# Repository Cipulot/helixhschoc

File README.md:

# Helix HS Choc

Hotswap Choc version of the Helix, a compact split ortholinear keyboard.

Original Helix keyboard was designed by [Makoto Kurauchi](https://github.com/MakotoKurauchi).

## Documents

* Build Guide - [JP](/Doc/buildguide_jp.md), [EN](/Doc/buildguide_en.md)
* Firmware - [JP](/Doc/firmware_jp.md), [EN](/Doc/firmware_en.md)
* Usage - [JP](/Doc/usage_jp.md), [EN](/Doc/usage_en.md)

## Tool & Data

* [PCB Data](/PCB)
* [Case Data](/Case)
* [Font Converter](/FontConverter)

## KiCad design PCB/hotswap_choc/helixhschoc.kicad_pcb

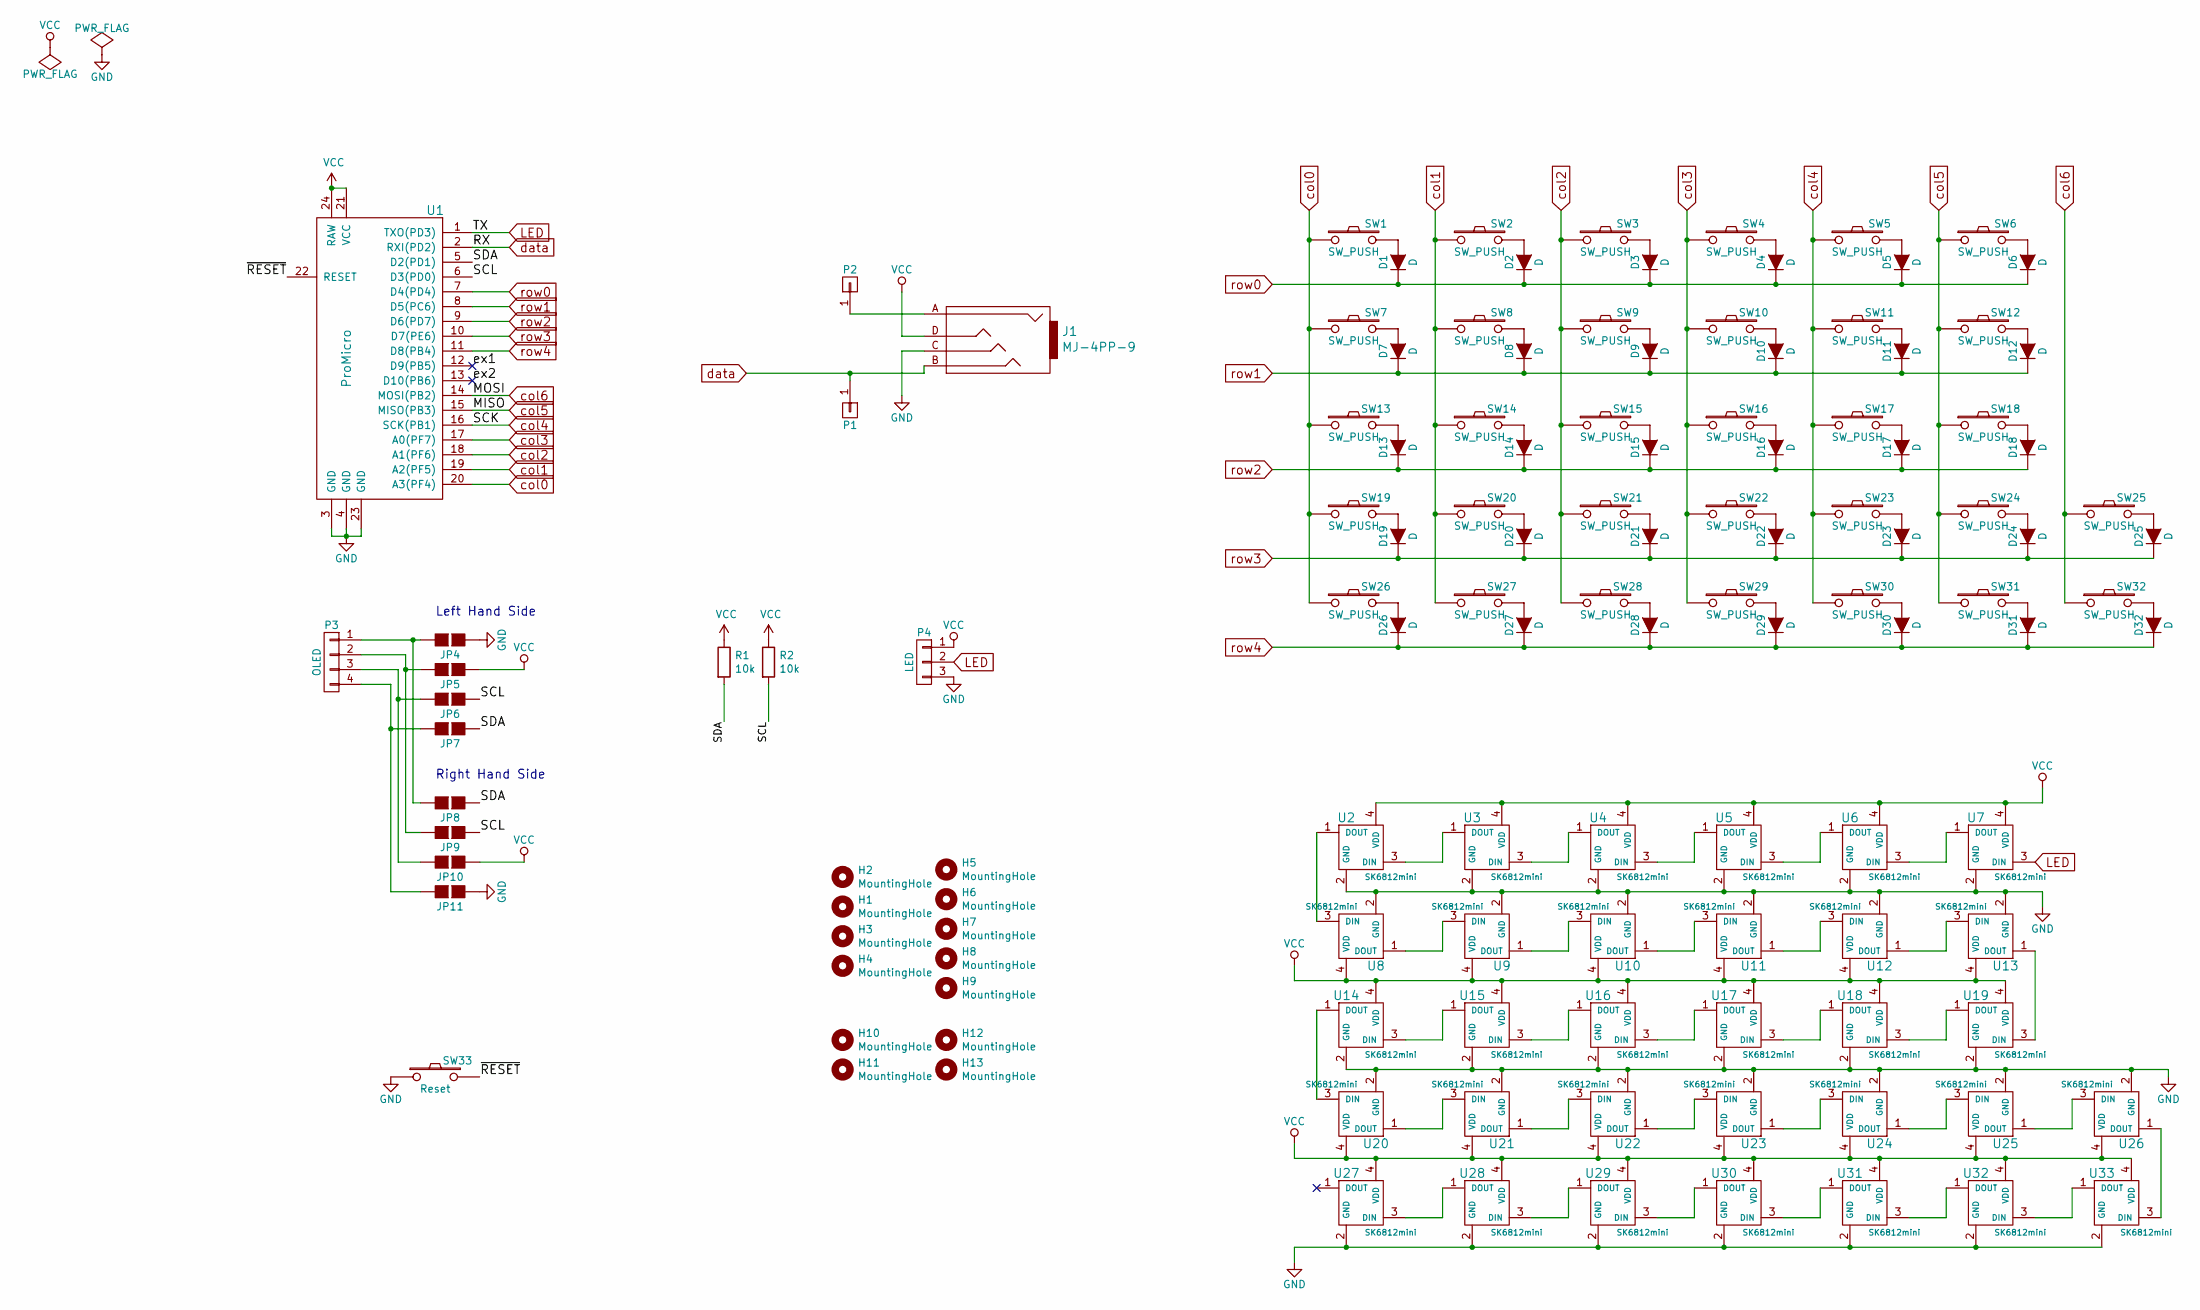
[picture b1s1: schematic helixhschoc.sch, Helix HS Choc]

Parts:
D1, D2, D3, D4, D5, D6, D7, D8, D9, D10, D11, D12, D13, D14, D15, D16, D17, D18, D19, D20, D21, D22, D23, D24, D25, D26, D27, D28, D29, D30, D31, D32: D; D_SOD-123_dual_reversed
H1, H2, H3, H4, H5, H6, H7, H8, H9: MountingHole; HOLE_M2_TH
H10, H11, H12, H13: MountingHole; HOLE_M2
J1: MJ-4PP-9
JP4, JP11: GND; Jumper_Small
JP5, JP10: VCC; Jumper_Small
JP6, JP9: SCL; Jumper_Small
JP7, JP8: SDA; Jumper_Small
P1, P2: CONN_01X01; Pin_Small
P3: OLED; OLED_Small
P4: LED; LED_Strip_Pad
R1, R2: 10k; R_0805_2012Metric
SW1, SW2, SW3, SW4, SW5, SW6, SW7, SW8, SW9, SW10, SW11, SW12, SW13, SW14, SW15, SW16, SW17, SW18, SW19, SW20, SW21, SW22, SW23, SW24, SW25, SW26, SW27, SW28, SW29, SW30, SW31, SW32: SW_PUSH; Kailh_socket_PG1350_reversible_LEFT_nosilkangle
SW33: Reset; SW_3.5x6.0_TH
U1: ProMicro; Sparkfun_Pro_Micro_reversible
U2, U3, U4, U5, U6, U7, U8, U9, U10, U11, U12, U13, U14, U15, U16, U17, U18, U19, U20, U21, U22, U23, U24, U25, U26, U27, U28, U29, U30, U31, U32, U33: SK6812mini; SK6812MINI_rev

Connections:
/SCL: JP6.1 (G1), JP9.1 (G1), R2.2, U1.6 (D3(PD0)); also elsewhere on the board
/SDA: JP7.1 (G1), JP8.1 (G1), R1.2, U1.5 (D2(PD1)); also elsewhere on the board
/ex1: U1.12 (D9(PB5))
/ex2: U1.13 (D10(PB6))
/~RESET: SW33.2, U1.22 (RESET)
GND: J1.C, JP4.1 (G1), JP11.1 (G1), P4.3, SW33.1, U1.3 (GND), U1.4 (GND), U1.23 (GND), U2.2 (GND), U3.2 (GND), U4.2 (GND), U5.2 (GND), U6.2 (GND), U7.2 (GND), U8.2 (GND), U9.2 (GND), U10.2 (GND), U11.2 (GND), U12.2 (GND), U13.2 (GND), U14.2 (GND), U15.2 (GND), U16.2 (GND), U17.2 (GND), U18.2 (GND), U19.2 (GND), U20.2 (GND), U21.2 (GND), U22.2 (GND), U23.2 (GND), U24.2 (GND), U25.2 (GND), U26.2 (GND), U27.2 (GND), U28.2 (GND), U29.2 (GND), U30.2 (GND), U31.2 (GND), U32.2 (GND), U33.2 (GND)
LED: P4.2, U1.1 (TXO(PD3)), U7.3 (DIN)
unnamed: D1.2 (A), SW1.2
unnamed: D2.2 (A), SW2.2
unnamed: D3.2 (A), SW3.2
unnamed: D4.2 (A), SW4.2
unnamed: D5.2 (A), SW5.2
unnamed: D6.2 (A), SW6.2
unnamed: D7.2 (A), SW7.2
unnamed: D8.2 (A), SW8.2
unnamed: D9.2 (A), SW9.2
unnamed: D10.2 (A), SW10.2
unnamed: D11.2 (A), SW11.2
unnamed: D12.2 (A), SW12.2
unnamed: D13.2 (A), SW13.2
unnamed: D14.2 (A), SW14.2
unnamed: D15.2 (A), SW15.2
unnamed: D16.2 (A), SW16.2
unnamed: D17.2 (A), SW17.2
unnamed: D18.2 (A), SW18.2
unnamed: D19.2 (A), SW19.2
unnamed: D20.2 (A), SW20.2
unnamed: D21.2 (A), SW21.2
unnamed: D22.2 (A), SW22.2
unnamed: D23.2 (A), SW23.2
unnamed: D24.2 (A), SW24.2
unnamed: D25.2 (A), SW25.2
unnamed: D26.2 (A), SW26.2
unnamed: D27.2 (A), SW27.2
unnamed: D28.2 (A), SW28.2
unnamed: D29.2 (A), SW29.2
unnamed: D30.2 (A), SW30.2
unnamed: D31.2 (A), SW31.2
unnamed: D32.2 (A), SW32.2
unnamed: J1.A, P2.1
unnamed: JP4.2 (G2), JP8.2 (G2), P3.1
unnamed: JP5.2 (G2), JP9.2 (G2), P3.2
unnamed: JP6.2 (G2), JP10.2 (G2), P3.3
unnamed: JP7.2 (G2), JP11.2 (G2), P3.4
unnamed: U2.1 (DOUT), U8.3 (DIN)
unnamed: U2.3 (DIN), U3.1 (DOUT)
unnamed: U3.3 (DIN), U4.1 (DOUT)
unnamed: U4.3 (DIN), U5.1 (DOUT)
unnamed: U5.3 (DIN), U6.1 (DOUT)
unnamed: U6.3 (DIN), U7.1 (DOUT)
unnamed: U8.1 (DOUT), U9.3 (DIN)
unnamed: U10.1 (DOUT), U11.3 (DIN)
unnamed: U9.1 (DOUT), U10.3 (DIN)
unnamed: U11.1 (DOUT), U12.3 (DIN)
unnamed: U12.1 (DOUT), U13.3 (DIN)
unnamed: U13.1 (DOUT), U19.3 (DIN)
unnamed: U14.1 (DOUT), U20.3 (DIN)
unnamed: U14.3 (DIN), U15.1 (DOUT)
unnamed: U15.3 (DIN), U16.1 (DOUT)
unnamed: U16.3 (DIN), U17.1 (DOUT)
unnamed: U17.3 (DIN), U18.1 (DOUT)
unnamed: U18.3 (DIN), U19.1 (DOUT)
unnamed: U20.1 (DOUT), U21.3 (DIN)
unnamed: U21.1 (DOUT), U22.3 (DIN)
unnamed: U22.1 (DOUT), U23.3 (DIN)
unnamed: U23.1 (DOUT), U24.3 (DIN)
unnamed: U24.1 (DOUT), U25.3 (DIN)
unnamed: U25.1 (DOUT), U26.3 (DIN)
unnamed: U26.1 (DOUT), U33.3 (DIN)
unnamed: U27.3 (DIN), U28.1 (DOUT)
unnamed: U28.3 (DIN), U29.1 (DOUT)
unnamed: U29.3 (DIN), U30.1 (DOUT)
unnamed: U30.3 (DIN), U31.1 (DOUT)
unnamed: U31.3 (DIN), U32.1 (DOUT)
unnamed: U32.3 (DIN), U33.1 (DOUT)
VCC: J1.D, JP5.1 (G1), JP10.1 (G1), P4.1, R1.1, R2.1, U1.21 (VCC), U1.24 (RAW), U2.4 (VDD), U3.4 (VDD), U4.4 (VDD), U5.4 (VDD), U6.4 (VDD), U7.4 (VDD), U8.4 (VDD), U9.4 (VDD), U10.4 (VDD), U11.4 (VDD), U12.4 (VDD), U13.4 (VDD), U14.4 (VDD), U15.4 (VDD), U16.4 (VDD), U17.4 (VDD), U18.4 (VDD), U19.4 (VDD), U20.4 (VDD), U21.4 (VDD), U22.4 (VDD), U23.4 (VDD), U24.4 (VDD), U25.4 (VDD), U26.4 (VDD), U27.4 (VDD), U28.4 (VDD), U29.4 (VDD), U30.4 (VDD), U31.4 (VDD), U32.4 (VDD), U33.4 (VDD); also elsewhere on the board
col0: SW1.1, SW7.1, SW13.1, SW19.1, SW26.1, U1.20 (A3(PF4))
col1: SW2.1, SW8.1, SW14.1, SW20.1, SW27.1, U1.19 (A2(PF5))
col2: SW3.1, SW9.1, SW15.1, SW21.1, SW28.1, U1.18 (A1(PF6))
col3: SW4.1, SW10.1, SW16.1, SW22.1, SW29.1, U1.17 (A0(PF7))
col4: SW5.1, SW11.1, SW17.1, SW23.1, SW30.1, U1.16 (SCK(PB1))
col5: SW6.1, SW12.1, SW18.1, SW24.1, SW31.1, U1.15 (MISO(PB3))
col6: SW25.1, SW32.1, U1.14 (MOSI(PB2))
data: J1.B, P1.1, U1.2 (RXI(PD2))
row0: D1.1 (K), D2.1 (K), D3.1 (K), D4.1 (K), D5.1 (K), D6.1 (K), U1.7 (D4(PD4))
row1: D7.1 (K), D8.1 (K), D9.1 (K), D10.1 (K), D11.1 (K), D12.1 (K), U1.8 (D5(PC6))
row2: D13.1 (K), D14.1 (K), D15.1 (K), D16.1 (K), D17.1 (K), D18.1 (K), U1.9 (D6(PD7))
row3: D19.1 (K), D20.1 (K), D21.1 (K), D22.1 (K), D23.1 (K), D24.1 (K), D25.1 (K), U1.10 (D7(PE6))
row4: D26.1 (K), D27.1 (K), D28.1 (K), D29.1 (K), D30.1 (K), D31.1 (K), D32.1 (K), U1.11 (D8(PB4))

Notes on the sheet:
Left Hand Side
Right Hand Side

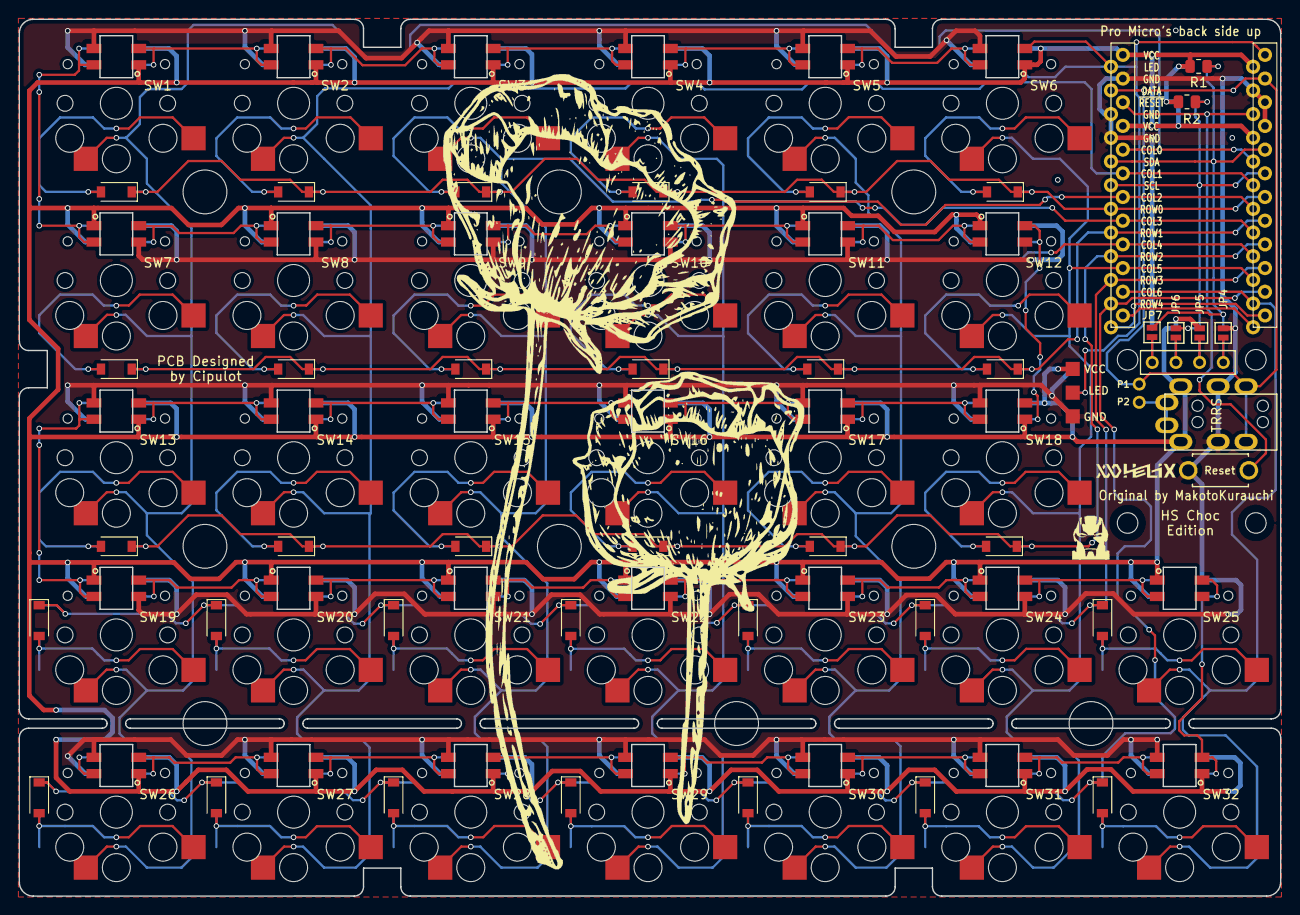
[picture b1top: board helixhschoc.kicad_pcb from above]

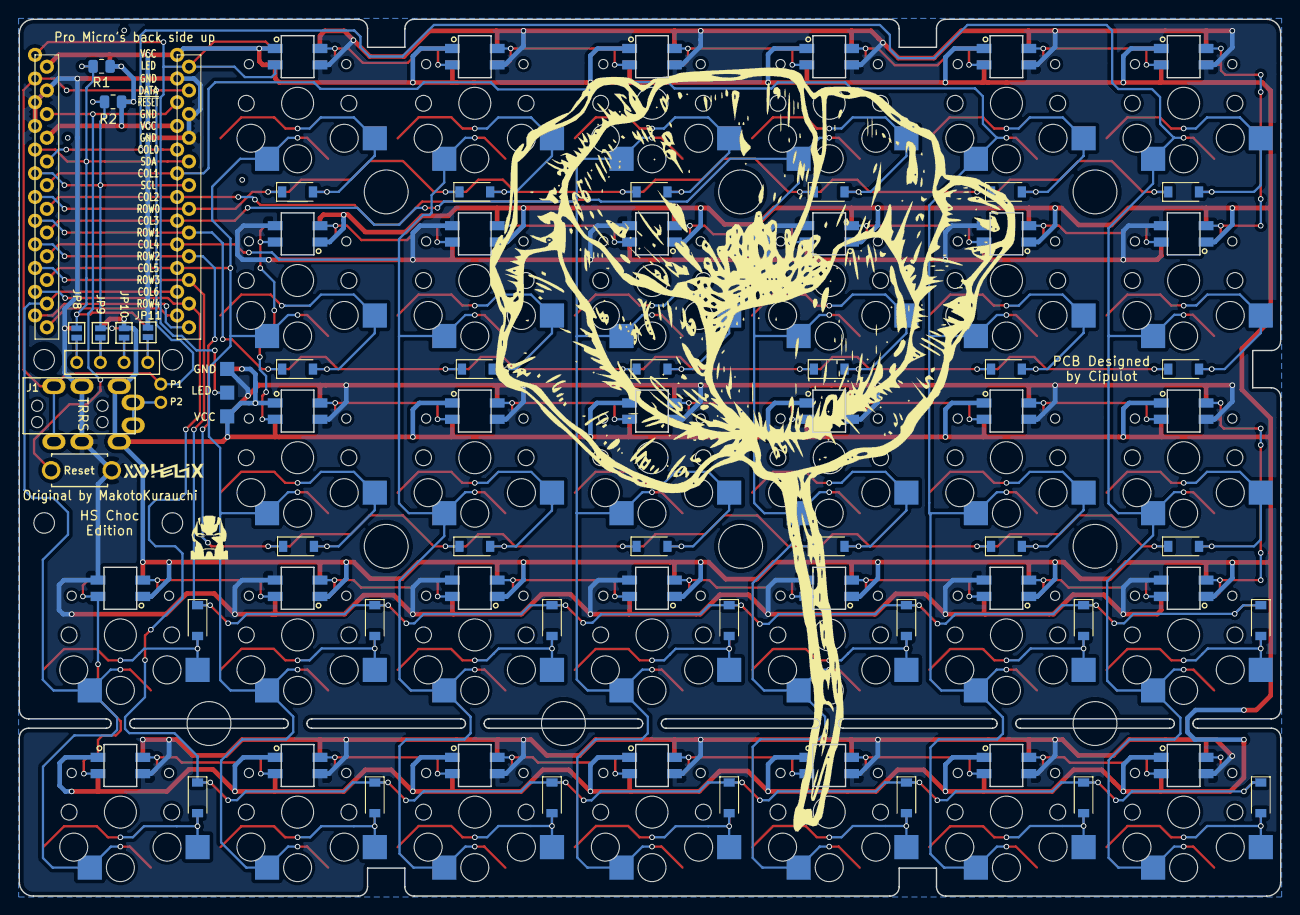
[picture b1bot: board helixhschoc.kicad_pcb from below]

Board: 2 copper layers, 135.2 x 94.0 mm, 128 parts (6 on the bottom side), 87 nets.

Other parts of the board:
R1#2, R2#2: 10k; R_0805_2012Metric

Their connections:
/SCL: R2#2.2; also elsewhere on the board
/SDA: R1#2.2; also elsewhere on the board
VCC: R1#2.1, R2#2.1; also elsewhere on the board

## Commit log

2021-12-16 Add submodule
2021-12-17 3D Print Case `.stl` files
2021-12-17 Font Converter Tools
    MIT Licensed by [Makoto Kurauchi](https://github.com/MakotoKurauchi)
2021-12-17 Add of PCB renders
2021-12-17 Add PCB Project
2021-12-22 Update cipulot_kicad_parts
2021-12-22 Add of font file
2021-12-22 PCB WIP
2021-12-23 Pcb update
2021-12-23 Images upload and reorganization
2021-12-24 Update libs
2021-12-24 Update 3d model and some wiring
2021-12-24 Hex files upload
2021-12-24 Update PCB
2021-12-24 Updated render images
2021-12-27 KiCad6 compatible project
2022-01-06 Case for 4-row

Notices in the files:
PCB/hotswap_choc/helixhschoc.sch:
Copyright © 2021 Cipulot
